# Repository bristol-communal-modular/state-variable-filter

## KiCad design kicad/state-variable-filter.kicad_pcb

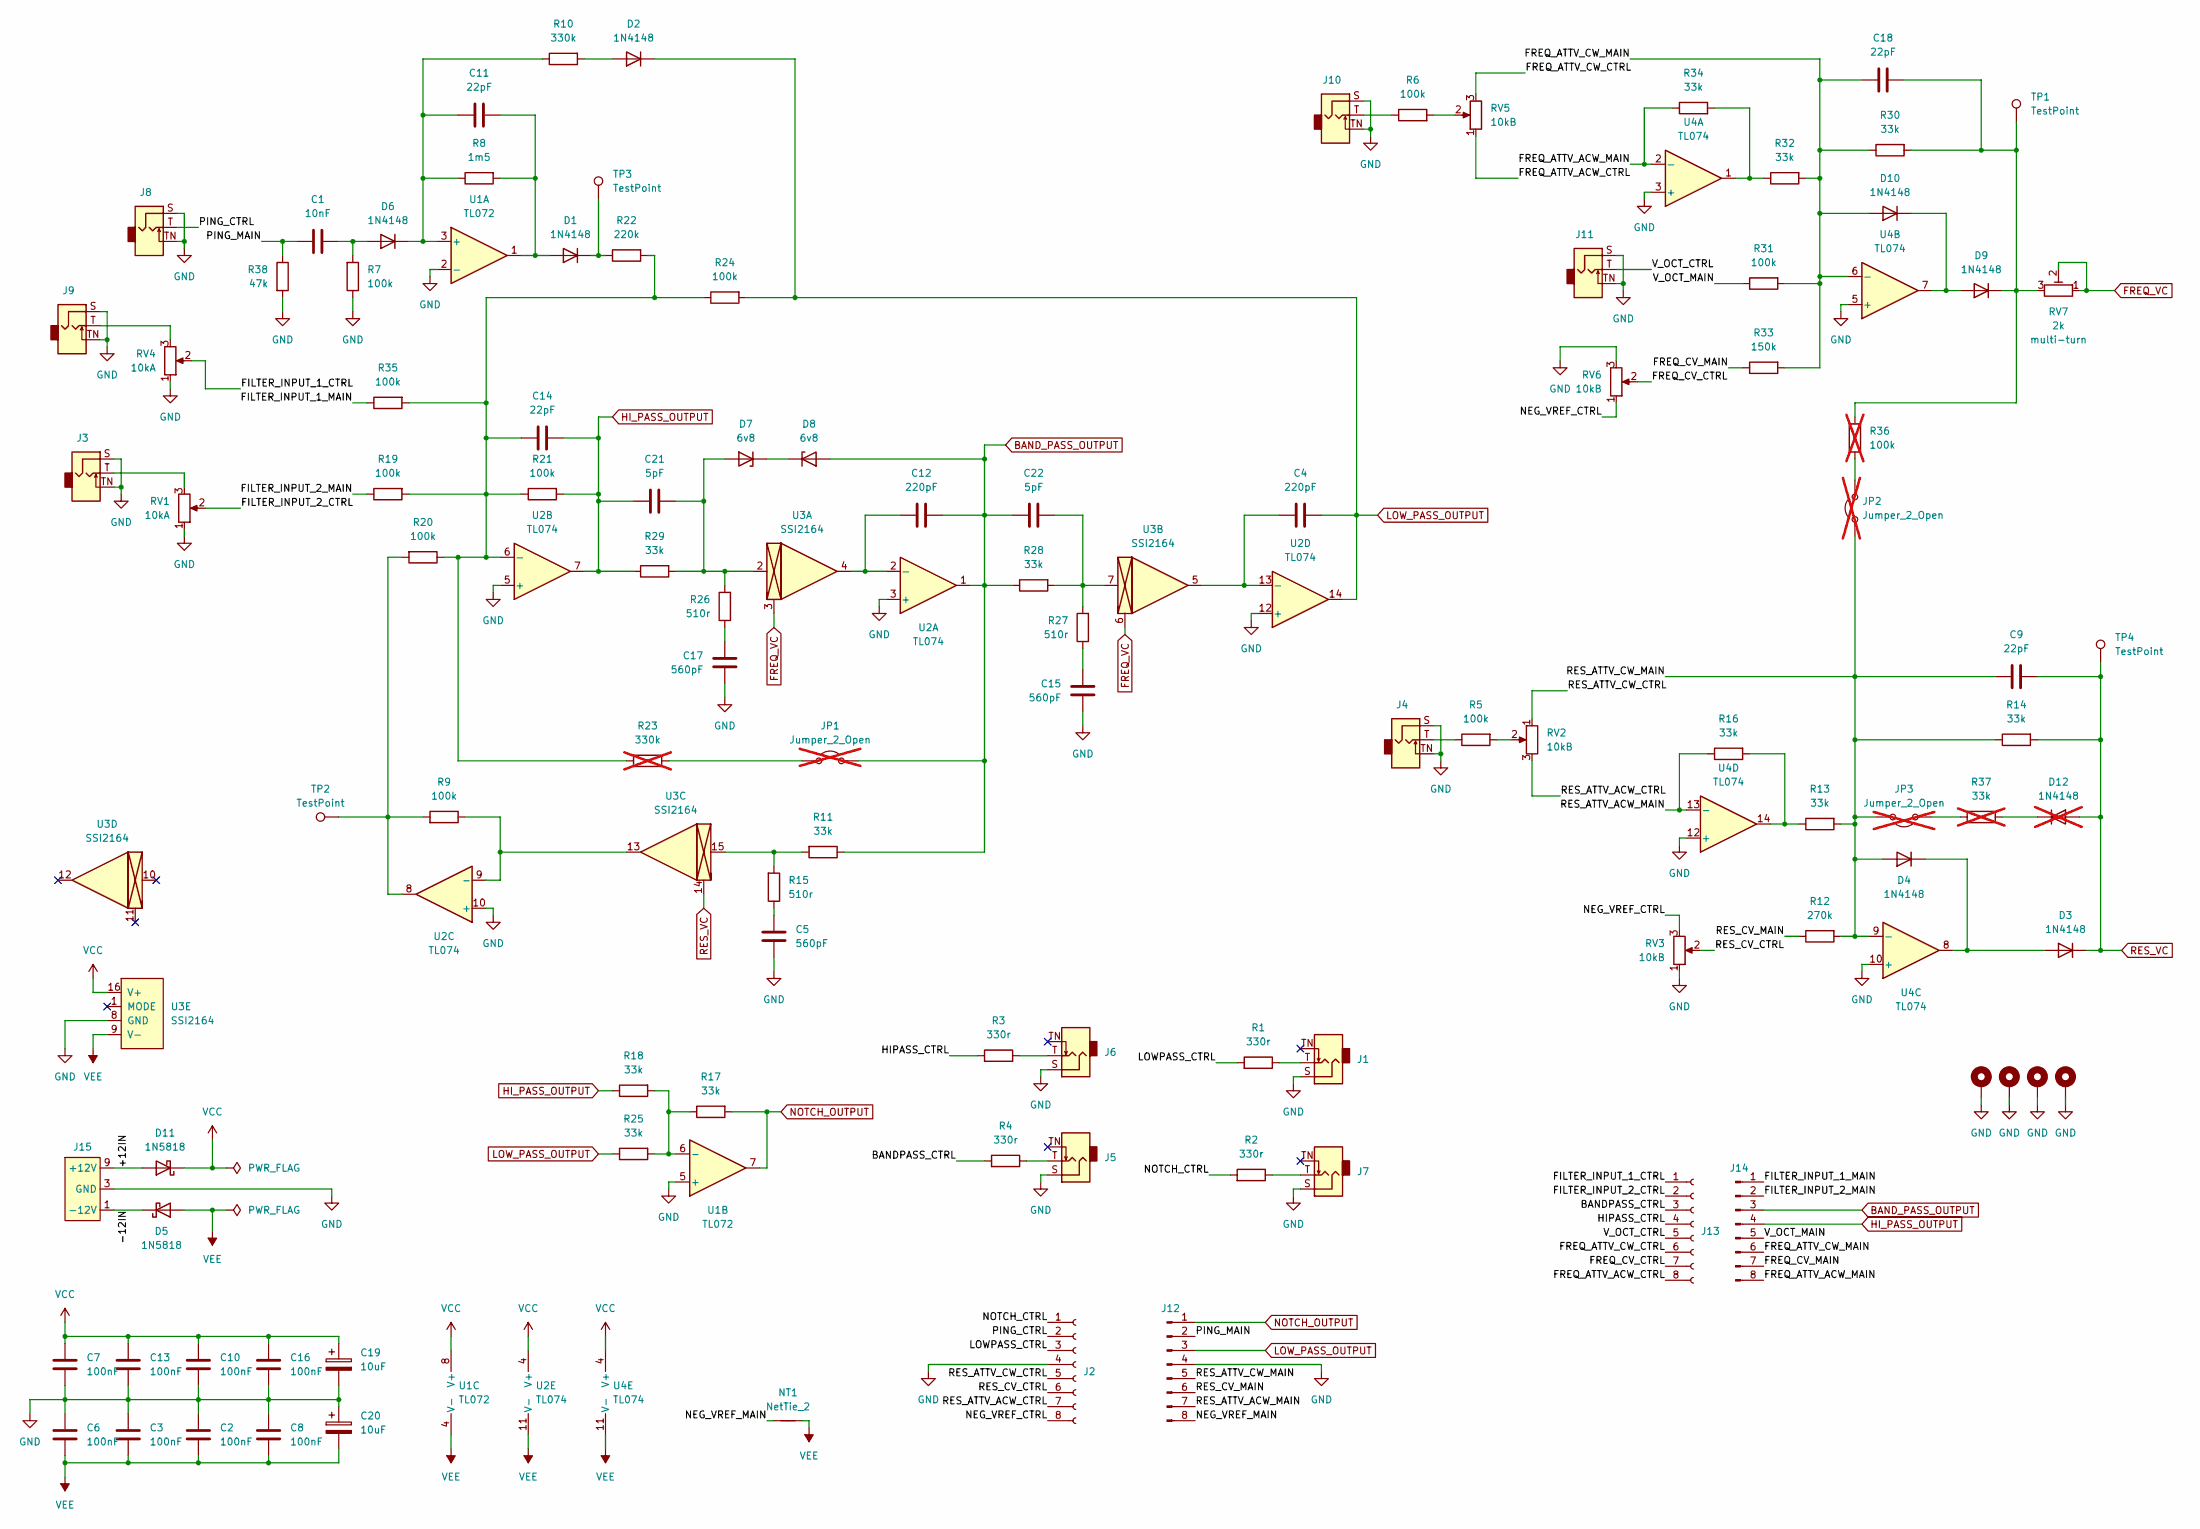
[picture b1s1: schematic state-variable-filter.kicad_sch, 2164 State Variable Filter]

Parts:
C1: 10nF; C_Rect_L7.0mm_W2.5mm_P5.00mm; Tolerance 5%
C2, C3, C6, C7, C8, C10, C13, C16: 100nF; C_Rect_L7.0mm_W2.5mm_P5.00mm; Tolerance 5%
C4, C12: 220pF; C_Rect_L7.0mm_W4.5mm_P5.00mm; Tolerance 1%
C5, C15, C17: 560pF; C_Rect_L7.0mm_W2.5mm_P5.00mm; Tolerance 5%
C9, C11, C14, C18: 22pF; C_Rect_L7.0mm_W2.5mm_P5.00mm; Tolerance 5%
C19, C20: 10uF; CP_Radial_D5.0mm_P2.00mm
C21, C22: 5pF; C_Rect_L7.0mm_W2.5mm_P5.00mm; Tolerance 5%
D1, D2, D3, D4, D6, D9, D10: 1N4148; D_DO-35_SOD27_P7.62mm_Horizontal
D5, D11: 1N5818; D_DO-41_SOD81_P10.16mm_Horizontal
D7, D8: 6v8; D_DO-35_SOD27_P7.62mm_Horizontal
D12: 1N4148; D_DO-35_SOD27_P7.62mm_Horizontal; not fitted
H1, H2, H3, H4: MountingHole_Pad; MountingHole_3.2mm_M3_DIN965_Pad
J1, J3, J4, J5, J6, J7, J8, J9, J10, J11: AudioJack2_SwitchT; Jack_3.5mm_QingPu_WQP-PJ398SM_Vertical
J2, J13: Conn_01x08_Socket; PinSocket_1x08_P2.54mm_Vertical
J12, J14: Conn_01x08_Pin; PinHeader_1x08_P2.54mm_Vertical
J15: Conn_02x05_Odd_Even; Eurorack_Power_IDC-Header_2x05_P2.54mm_Vertical
JP1, JP2, JP3: Jumper_2_Open; PinHeader_1x02_P2.54mm_Vertical; not fitted
NT1: NetTie_2; NetTie-2_SMD_Pad0.5mm
R1, R2, R3, R4: 330r; R_Axial_DIN0207_L6.3mm_D2.5mm_P10.16mm_Horizontal; Tolerance 1%
R5, R6, R7, R9, R19, R20, R21, R24, R31, R35: 100k; R_Axial_DIN0207_L6.3mm_D2.5mm_P10.16mm_Horizontal; Tolerance 1%
R8: 1m5; R_Axial_DIN0207_L6.3mm_D2.5mm_P10.16mm_Horizontal; Tolerance 1%
R10: 330k; R_Axial_DIN0207_L6.3mm_D2.5mm_P10.16mm_Horizontal; Tolerance 1%
R11, R13, R14, R16, R17, R18, R25, R28, R29, R30, R32, R34: 33k; R_Axial_DIN0207_L6.3mm_D2.5mm_P10.16mm_Horizontal; Tolerance 1%
R12: 270k; R_Axial_DIN0207_L6.3mm_D2.5mm_P10.16mm_Horizontal; Tolerance 1%
R15, R26, R27: 510r; R_Axial_DIN0207_L6.3mm_D2.5mm_P10.16mm_Horizontal; Tolerance 1%
R22: 220k; R_Axial_DIN0207_L6.3mm_D2.5mm_P10.16mm_Horizontal; Tolerance 1%
R23: 330k; R_Axial_DIN0207_L6.3mm_D2.5mm_P10.16mm_Horizontal; Tolerance 1%; not fitted
R33: 150k; R_Axial_DIN0207_L6.3mm_D2.5mm_P10.16mm_Horizontal; Tolerance 1%
R36: 100k; R_Axial_DIN0207_L6.3mm_D2.5mm_P10.16mm_Horizontal; Tolerance 1%; not fitted
R37: 33k; R_Axial_DIN0207_L6.3mm_D2.5mm_P10.16mm_Horizontal; Tolerance 1%; not fitted
R38: 47k; R_Axial_DIN0207_L6.3mm_D2.5mm_P10.16mm_Horizontal; Tolerance 1%
RV1, RV4: 10kA; Potentiometer_Alpha_RD901F-40-00D_Single_Vertical
RV2, RV3, RV5, RV6: 10kB; Potentiometer_Alpha_RD901F-40-00D_Single_Vertical
RV7: 2k; Potentiometer_Vishay_T93YB_Vertical
TP1, TP2, TP3, TP4: TestPoint; TestPoint_Loop_D2.50mm_Drill1.0mm_LowProfile
U1: TL072; DIP-8_W7.62mm_Socket
U2, U4: TL074; DIP-14_W7.62mm_Socket
U3: SSI2164; DIP-16_W7.62mm_Socket

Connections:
/+12IN: D11.2 (A), J15.9 (+12V), J15.10 (+12V)
/-12IN: D5.1 (K), J15.1 (-12V), J15.2 (-12V)
/BANDPASS_CTRL: J13.3, R4.2
/FILTER_INPUT_1_CTRL: J13.1, RV4.2
/FILTER_INPUT_1_MAIN: J14.1, R35.2
/FILTER_INPUT_2_CTRL: J13.2, RV1.2
/FILTER_INPUT_2_MAIN: J14.2, R19.2
/FREQ_ATTV_ACW_CTRL: J13.8, RV5.1
/FREQ_ATTV_ACW_MAIN: J14.8, R34.2, U4.2 (-)
/FREQ_ATTV_CW_CTRL: J13.6, RV5.3
/FREQ_ATTV_CW_MAIN: C18.1, D10.2 (A), J14.6, R30.2, R31.1, R32.1, R33.1, U4.6 (-)
/FREQ_CV_CTRL: J13.7, RV6.2
/FREQ_CV_MAIN: J14.7, R33.2
/HIPASS_CTRL: J13.4, R3.2
/LOWPASS_CTRL: J2.3, R1.2
/NEG_VREF_CTRL: J2.8, RV3.3, RV6.1
/NEG_VREF_MAIN: J12.8, NT1.1
/NOTCH_CTRL: J2.1, R2.2
/PING_CTRL: J2.2, J8.T
/PING_MAIN: C1.1, J12.2, R38.2
/RES_ATTV_ACW_CTRL: J2.7, RV2.3
/RES_ATTV_ACW_MAIN: J12.7, R16.2, U4.13 (-)
/RES_ATTV_CW_CTRL: J2.5, RV2.1
/RES_ATTV_CW_MAIN: C9.1, D4.2 (A), J12.5, JP2.1 (A), JP3.2 (B), R12.1, R13.1, R14.2, U4.9 (-)
/RES_CV_CTRL: J2.6, RV3.2
/RES_CV_MAIN: J12.6, R12.2
/V_OCT_CTRL: J11.T, J13.5
/V_OCT_MAIN: J14.5, R31.2
BAND_PASS_OUTPUT: C12.2, C22.1, D8.2 (A), J14.3, JP1.2 (B), R11.2, R28.2, U2.1
FREQ_VC: RV7.1, RV7.2, U3.3, U3.6
GND: C2.1, C3.1, C5.2, C6.1, C7.2, C8.1, C10.2, C13.2, C15.2, C16.2, C17.2, C19.2, C20.1, H1.1, H2.1, H3.1, H4.1, J1.S, J2.4, J3.S, J3.TN, J4.S, J4.TN, J5.S, J6.S, J7.S, J8.S, J8.TN, J9.S, J9.TN, J10.S, J10.TN, J11.S, J11.TN, J12.4, J15.3 (GND), J15.4 (GND), J15.5 (GND), J15.6 (GND), J15.7 (GND), J15.8 (GND), R7.2, R38.1, RV1.1, RV3.1, RV4.1, RV6.3, U1.2 (-), U1.5 (+), U2.3 (+), U2.5 (+), U2.10 (+), U2.12 (+), U3.8 (GND), U4.3 (+), U4.5 (+), U4.10 (+), U4.12 (+)
HI_PASS_OUTPUT: C14.2, C21.1, J14.4, R18.2, R21.1, R29.2, U2.7
LOW_PASS_OUTPUT: C4.2, D2.1 (K), J12.3, R24.1, R25.2, U2.14
NOTCH_OUTPUT: J12.1, R17.1, U1.7
unnamed: C5.1, R15.2
unnamed: C15.1, R27.2
unnamed: C17.1, R26.2
unnamed: C22.2, R27.1, R28.1, U3.7
unnamed: C11.2, D1.2 (A), R8.1, U1.1
unnamed: D1.1 (K), R22.2, TP3.1
unnamed: D2.2 (A), R10.1
unnamed: D3.2 (A), D4.1 (K), U4.8
unnamed: C1.2, D6.2 (A), R7.1
unnamed: C11.1, D6.1 (K), R8.2, R10.2, U1.3 (+)
unnamed: C21.2, D7.2 (A), R26.1, R29.1, U3.2
unnamed: D7.1 (K), D8.1 (K)
unnamed: C18.2, D9.1 (K), R30.1, R36.1, RV7.3, TP1.1
unnamed: D9.2 (A), D10.1 (K), U4.7
unnamed: D12.1 (K), R37.1
unnamed: J1.T, R1.1
unnamed: J3.T, RV1.3
unnamed: J4.T, R5.2
unnamed: J5.T, R4.1
unnamed: J6.T, R3.1
unnamed: J7.T, R2.1
unnamed: J9.T, RV4.3
unnamed: J10.T, R6.2
unnamed: JP1.1 (A), R23.1
unnamed: JP2.2 (B), R36.2
unnamed: JP3.1 (A), R37.2
unnamed: R5.1, RV2.2
unnamed: R6.1, RV5.2
unnamed: R11.1, R15.1, U3.15
unnamed: R13.2, R16.1, U4.14
unnamed: R9.1, R20.1, TP2.1, U2.8
unnamed: R32.2, R34.1, U4.1
unnamed: R17.2, R18.1, R25.1, U1.6 (-)
unnamed: C12.1, U2.2 (-), U3.4
unnamed: C14.1, R19.1, R20.2, R21.2, R22.1, R23.2, R24.2, R35.1, U2.6 (-)
unnamed: R9.2, U2.9 (-), U3.13
unnamed: C4.1, U2.13 (-), U3.5
RES_VC: C9.2, D3.1 (K), D12.2 (A), R14.1, TP4.1, U3.14
VCC: C7.1, C10.1, C13.1, C16.1, C19.1, D11.1 (K), U1.8 (V+), U2.4 (V+), U3.16 (V+), U4.4 (V+)
VEE: C2.2, C3.2, C6.2, C8.2, C20.2, D5.2 (A), NT1.2, U1.4 (V-), U2.11 (V-), U3.9 (V-), U4.11 (V-)

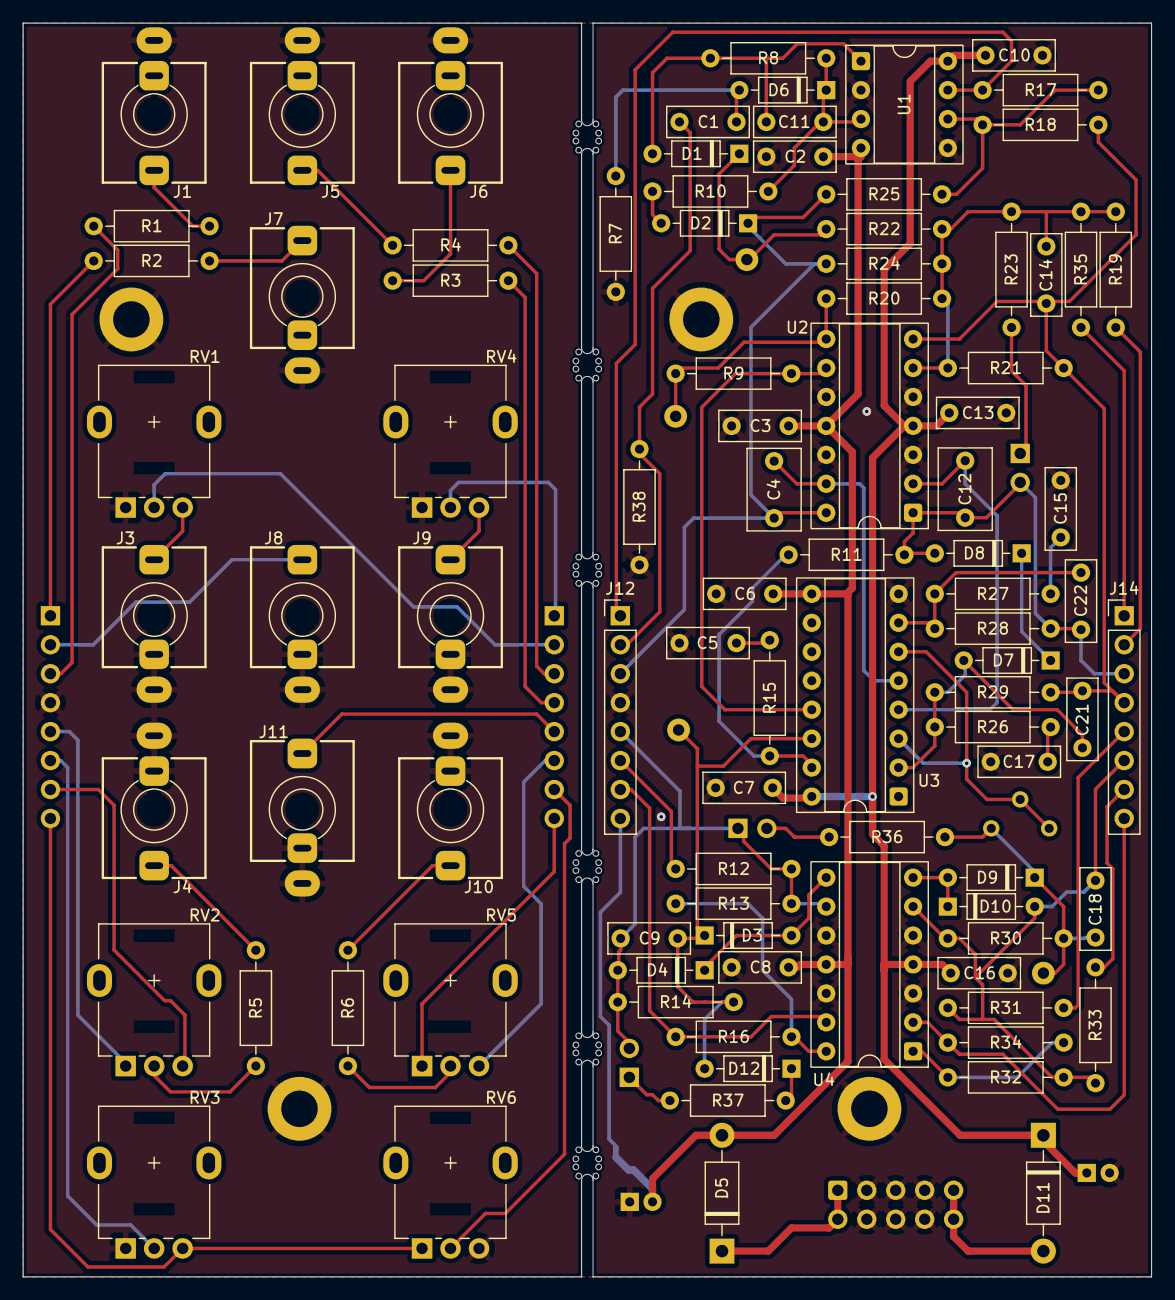
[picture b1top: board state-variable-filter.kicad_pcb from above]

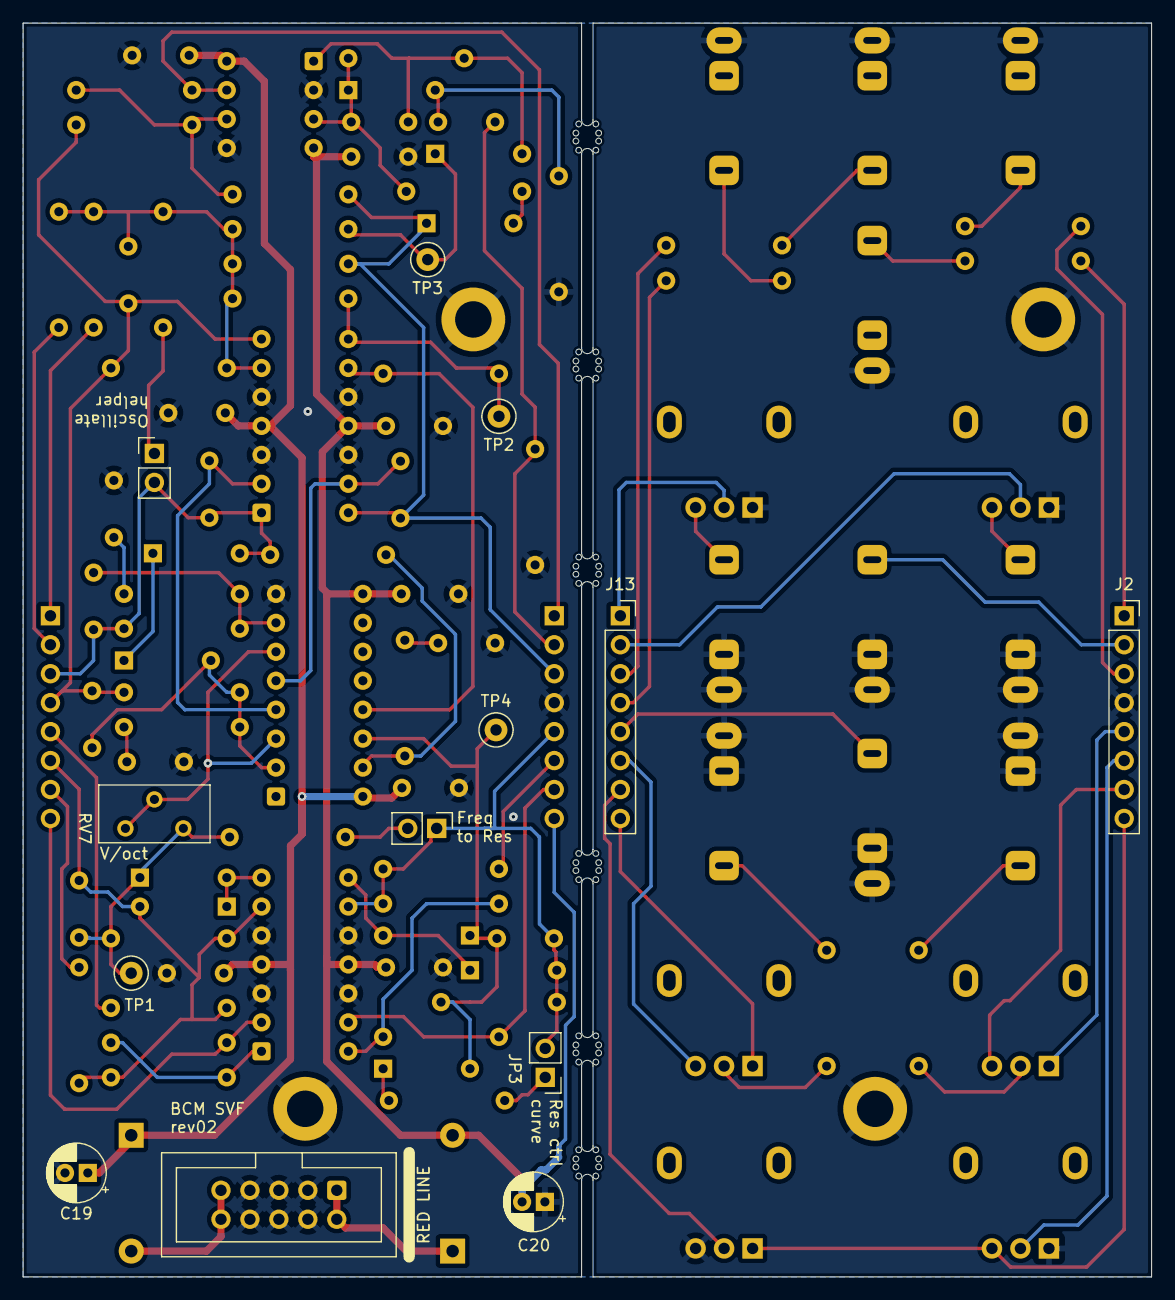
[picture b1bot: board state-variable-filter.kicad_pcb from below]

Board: 2 copper layers, 99.0 x 110.0 mm, 116 parts (14 on the bottom side), 74 nets.

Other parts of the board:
mouse-bite-1mm-slot, mouse-bite-1mm-slot#2, mouse-bite-1mm-slot#3, mouse-bite-1mm-slot#4, mouse-bite-1mm-slot#5, mouse-bite-1mm-slot#6: VAL**; mouse-bite-1mm-slot

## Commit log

2025-12-06 Moving kicad files into subfolder
2025-12-15 Updating hardware design
2025-12-15 Adding filter design docs
2025-12-15 Adding beginning of panel design files
2025-12-24 Updating design
    * Adding resonance control curve jumper
    * improving layout
2025-12-24 Adding basic panel design
2026-01-03 Fixing a couple issues with schematic and layout
2026-01-03 Adding panel PCB
2026-01-03 Plotting gerbers
2026-02-24 minor tweaks
2026-02-24 Adding BOM
2026-02-26 Fixing minor BOM value issues
2026-03-02 Updating schematic after value tweaks
    and regenerating BOMs
2026-03-02 Adding notes on fixes
2026-03-02 Updating with rev02 fixes
2026-03-02 Regenerating BOMs
2026-03-02 Regenerating gerbers for rev02

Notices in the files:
kicad/state-variable-filter.kicad_pcb:
creativecommons.org/licenses/by/4.0
License: CC BY 4.0
